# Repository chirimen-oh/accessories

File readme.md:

# Accessories for CHIRIMEN

They are hardware accessories of CHIRIMEN, all open source blueprints and can be used on the CHIRIMEN environment. They are mainly intended for use with CHIRIMEN for RPi, but  general purpose and can be used in other environments.

- [prot-hat](forRaspberryPi3/prot-hat/)
- [rpi3GpioTester](forRaspberryPi3/rpi3GpioTester/)
- [Grove-adt7410](grove/adt7410/)
- [Grove-s11059](grove/s11059/)
- [RPi2SeinsmartRelayIF](others/RPi2SeinsmartRelayIF/)
- [dcfan-guide](others/dcfan-guide/)
- [neopixel_i2c_TH](others/neopixel_i2c_TH/)

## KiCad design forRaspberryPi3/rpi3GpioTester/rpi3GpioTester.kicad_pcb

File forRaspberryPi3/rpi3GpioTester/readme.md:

# CHIRIMEN for RPi Full Test Board

### OSHW 
- [OSHWA UID: JP000006](https://certification.oshwa.org/jp000008.html)

CHIRIMEN for Raspberry Piの、[テストスイート](https://github.com/chirimen-oh/chirimen-raspi3/tree/master/gc/testSet)を一気に通すための試験用基板です。

それ以外にもRaspberry Piのブレークアウトボード的に便利に使えるかもしれません。

## Size

100x100mm  2layers

## Version

0.5 (KiCad version:5.1.4)

## 基板の発注

Elecrow等の基板製造サービスに、基板のサイズ(100x100mm)、Layer数(=2)、厚みや色(お好みで)など必要事項を記載の上、Gerberディレクトリの内容をアーカイブしたものを添付して発注します。[詳細は、Webで検索](https://www.google.com/search?q=elecrow+%E7%99%BA%E6%B3%A8%E6%96%B9%E6%B3%95)

## Parts

この基板に以下のパーツを半田付けしてご利用ください

- Raspberry Pi 接続用
  - 2x20 ピンソケット x1 - [秋月電子](http://akizukidenshi.com/catalog/g/gC-00085/)
    - あるいは 2x20 連結ピンソケット x1 - [秋月電子](http://akizukidenshi.com/catalog/g/gC-02485/), [スイッチサイエンス](https://www.switch-science.com/catalog/2022/)
    - あるいは 2x20 スタッキングコネクタ x 1 - [秋月電子](http://akizukidenshi.com/catalog/g/gC-10702/)
- GPIO 試験用
  - LED x 17 (3mm砲弾型で設計, 14+3 で 2 色にすると使いやすい)
  - LED 用抵抗 470Ω x 17 (LEDに流したい電流によって調整してください(1KΩぐらいまでは光ると思います))
  - タクトスイッチ (4本足、黒) x 14 - [秋月電子](http://akizukidenshi.com/catalog/g/gP-03647/), [Amazon](https://www.amazon.co.jp/dp/B07SYHP9B4/), [AliExpress](https://ja.aliexpress.com/item/32845984040.html)
  - タクトスイッチ (4本足、白) x 3 - [秋月電子](http://akizukidenshi.com/catalog/g/gP-03648/), [Amazon](https://www.amazon.co.jp/dp/B07SYZCL8Q/), [AliExpress](https://ja.aliexpress.com/item/32847703781.html)
- Grove 接続用
  - メスソケット x 4 - [千石通商](https://www.sengoku.co.jp/mod/sgk_cart/detail.php?code=EEHD-4KKK), [Switch Science](https://www.switch-science.com/catalog/1122/)
- I2C 接続用
  - 1x4 ピンソケット x 16 (I2C 用) - [秋月電子](http://akizukidenshi.com/catalog/g/gC-10099/)
    - note: 分割ロングピンソケットを分割してもよいが見栄えは悪くなる - [秋月電子](http://akizukidenshi.com/catalog/goods/search.aspx?search=x&keyword=fhu-1)
- その他の接続用
  - 1x20 ピンヘッダ x 1 - [秋月電子 (1x40 を分割)](http://akizukidenshi.com/catalog/g/gC-00167/)
    - あるいは 1x20 ピンソケット x1 - [秋月電子](http://akizukidenshi.com/catalog/g/gC-03077/)
  - 1x12 ピンヘッダ x 1 - [秋月電子 (1x40 を分割)](http://akizukidenshi.com/catalog/g/gC-00167/) 
    - あるいは 1x12 ピンソケット x1 - [秋月電子](http://akizukidenshi.com/catalog/g/gC-10101/)
  - 1x4 ピンヘッダ x 6 - [秋月電子 (1x40 を分割)](http://akizukidenshi.com/catalog/g/gC-00167/) 

I2C デバイス接続用に用意しておくと便利なもの
- 4pin ジャンパワイヤ - [秋月電子](https://ja.aliexpress.com/item/32812824461.html)

そのほか、試験対象とする I2C デバイス一式をご用意ください

## PCB Assembly

### 極性に注意するパーツ

- LED : 基板のパターンで、□(四角いランド)がGND(-)です (LEDの短い足を挿す)
- Grove : 写真を参考に
- 2x20ピンソケット : 裏側に取り付けます

### その他のはんだ付けの留意点

コネクタやピンヘッダは、まずピン一本だけはんだ付けした後、浮き上がりや、傾きなどをコテを当てながら修正した後に、残りの全ピンをはんだ付けするときれいに仕上がります。LEDやタクトスイッチ、抵抗器も同様に処理すると良いでしょう。

Grove や I2C 接続用ソケットはまとめてマスキングテープや養生テープで固定してから半田付けを行うとまとめて半田付けし易いです。

I2C, GND, 5V, 3.3V などをピンヘッダとピンソケットのいずれにするかは好み次第ですが、予定と違うものを付けないよう注意しましょう。

GPIO のプルアップ (PU) とプルダウン (PD) はお好み (と手元のパーツの都合) で LED やタクトスイッチの色を変えると見やすくなります。

### 組み立て例

## 回路図

## License

CC by 4.0

## OSHWA (オープンソースハードウェア) 認証ID
https://certification.oshwa.org/jp000006.html

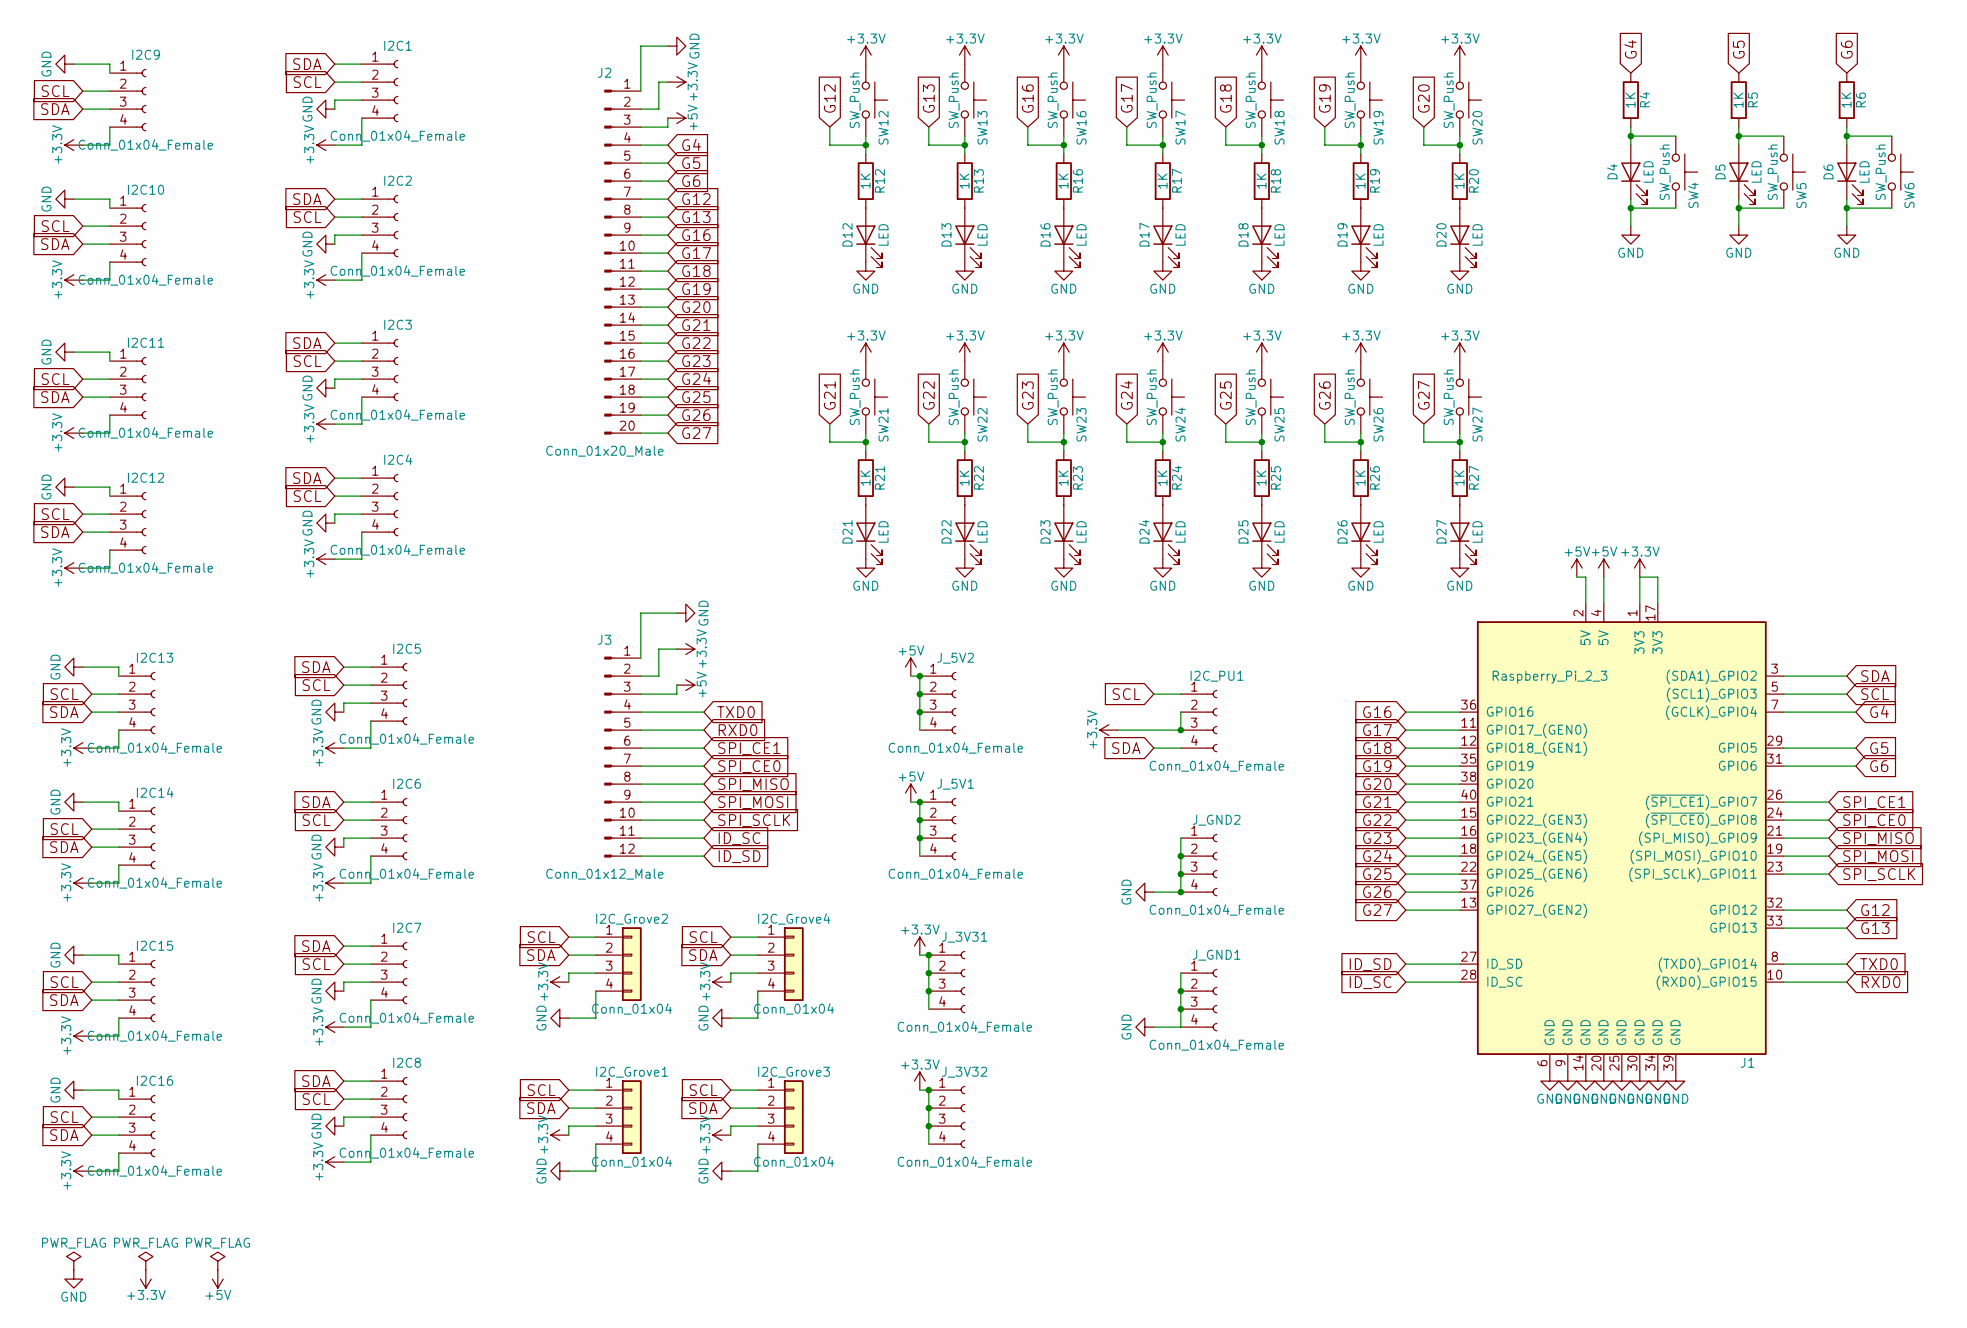
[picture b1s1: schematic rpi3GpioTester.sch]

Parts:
D4, D5, D6, D12, D13, D16, D17, D18, D19, D20, D21, D22, D23, D24, D25, D26, D27: LED; LED_D3.0mm
I2C1, I2C2, I2C3, I2C4, I2C5, I2C6, I2C7, I2C8, I2C9, I2C10, I2C11, I2C12, I2C13, I2C14, I2C15, I2C16, I2C_PU1: Conn_01x04_Female; Socket_Strip_Straight_1x04_Pitch2.54mm
I2C_Grove1, I2C_Grove2, I2C_Grove3, I2C_Grove4: Conn_01x04; Grove_1x04
J1: Raspberry_Pi_2_3; Socket_Strip_Straight_2x20_Pitch2.54mm
J2: Conn_01x20_Male; Pin_Header_Straight_1x20_Pitch2.54mm
J3: Conn_01x12_Male; Pin_Header_Straight_1x12_Pitch2.54mm
J_3V31, J_3V32, J_5V1, J_5V2: Conn_01x04_Female; Socket_Strip_Straight_1x04_Pitch2.54mm
J_GND1, J_GND2: Conn_01x04_Female; Socket_Strip_Straight_1x04_Pitch2.54mm
R4, R5, R6, R12, R13, R16, R17, R18, R19, R20, R21, R22, R23, R24, R25, R26, R27: 1K; R_Axial_DIN0207_L6.3mm_D2.5mm_P2.54mm_Vertical
SW4, SW5, SW6, SW12, SW13, SW16, SW17, SW18, SW19, SW20, SW21, SW22, SW23, SW24, SW25, SW26, SW27: SW_Push; SW_Tactile_Straight_KSA0Axx1LFTR

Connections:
+3V3: I2C1.4, I2C2.4, I2C3.4, I2C4.4, I2C5.4, I2C6.4, I2C7.4, I2C8.4, I2C9.4, I2C10.4, I2C11.4, I2C12.4, I2C13.4, I2C14.4, I2C15.4, I2C16.4, I2C_Grove1.3, I2C_Grove2.3, I2C_Grove3.3, I2C_Grove4.3, I2C_PU1.2, I2C_PU1.3, J1.1 (3V3), J1.17 (3V3), J2.2, J3.2, J_3V31.1, J_3V31.2, J_3V31.3, J_3V31.4, J_3V32.1, J_3V32.2, J_3V32.3, J_3V32.4, SW12.1, SW13.1, SW16.1, SW17.1, SW18.1, SW19.1, SW20.1, SW21.1, SW22.1, SW23.1, SW24.1, SW25.1, SW26.1, SW27.1
+5V: J1.2 (5V), J1.4 (5V), J2.3, J3.3, J_5V1.1, J_5V1.2, J_5V1.3, J_5V1.4, J_5V2.1, J_5V2.2, J_5V2.3, J_5V2.4
G4: J1.7 ((GCLK)_GPIO4), J2.4, R4.1
G5: J1.29 (GPIO5), J2.5, R5.1
G6: J1.31 (GPIO6), J2.6, R6.1
G12: J1.32 (GPIO12), J2.7, R12.1, SW12.2
G13: J1.33 (GPIO13), J2.8, R13.1, SW13.2
G16: J1.36 (GPIO16), J2.9, R16.1, SW16.2
G17: J1.11 (GPIO17_(GEN0)), J2.10, R17.1, SW17.2
G18: J1.12 (GPIO18_(GEN1)), J2.11, R18.1, SW18.2
G19: J1.35 (GPIO19), J2.12, R19.1, SW19.2
G20: J1.38 (GPIO20), J2.13, R20.1, SW20.2
G21: J1.40 (GPIO21), J2.14, R21.1, SW21.2
G22: J1.15 (GPIO22_(GEN3)), J2.15, R22.1, SW22.2
G23: J1.16 (GPIO23_(GEN4)), J2.16, R23.1, SW23.2
G24: J1.18 (GPIO24_(GEN5)), J2.17, R24.1, SW24.2
G25: J1.22 (GPIO25_(GEN6)), J2.18, R25.1, SW25.2
G26: J1.37 (GPIO26), J2.19, R26.1, SW26.2
G27: J1.13 (GPIO27_(GEN2)), J2.20, R27.1, SW27.2
GND: D4.1 (K), D5.1 (K), D6.1 (K), D12.1 (K), D13.1 (K), D16.1 (K), D17.1 (K), D18.1 (K), D19.1 (K), D20.1 (K), D21.1 (K), D22.1 (K), D23.1 (K), D24.1 (K), D25.1 (K), D26.1 (K), D27.1 (K), I2C1.3, I2C2.3, I2C3.3, I2C4.3, I2C5.3, I2C6.3, I2C7.3, I2C8.3, I2C9.1, I2C10.1, I2C11.1, I2C12.1, I2C13.1, I2C14.1, I2C15.1, I2C16.1, I2C_Grove1.4, I2C_Grove2.4, I2C_Grove3.4, I2C_Grove4.4, J1.6 (GND), J1.9 (GND), J1.14 (GND), J1.20 (GND), J1.25 (GND), J1.30 (GND), J1.34 (GND), J1.39 (GND), J2.1, J3.1, J_GND1.1, J_GND1.2, J_GND1.3, J_GND1.4, J_GND2.1, J_GND2.2, J_GND2.3, J_GND2.4, SW4.2, SW5.2, SW6.2
ID_SC: J1.28 (ID_SC), J3.11
ID_SD: J1.27 (ID_SD), J3.12
unnamed: D4.2 (A), R4.2, SW4.1
unnamed: D5.2 (A), R5.2, SW5.1
unnamed: D6.2 (A), R6.2, SW6.1
unnamed: D12.2 (A), R12.2
unnamed: D13.2 (A), R13.2
unnamed: D16.2 (A), R16.2
unnamed: D17.2 (A), R17.2
unnamed: D18.2 (A), R18.2
unnamed: D19.2 (A), R19.2
unnamed: D20.2 (A), R20.2
unnamed: D21.2 (A), R21.2
unnamed: D22.2 (A), R22.2
unnamed: D23.2 (A), R23.2
unnamed: D24.2 (A), R24.2
unnamed: D25.2 (A), R25.2
unnamed: D26.2 (A), R26.2
unnamed: D27.2 (A), R27.2
RXD0: J1.10 ((RXD0)_GPIO15), J3.5
SCL: I2C1.2, I2C2.2, I2C3.2, I2C4.2, I2C5.2, I2C6.2, I2C7.2, I2C8.2, I2C9.2, I2C10.2, I2C11.2, I2C12.2, I2C13.2, I2C14.2, I2C15.2, I2C16.2, I2C_Grove1.1, I2C_Grove2.1, I2C_Grove3.1, I2C_Grove4.1, I2C_PU1.1, J1.5 ((SCL1)_GPIO3)
SDA: I2C1.1, I2C2.1, I2C3.1, I2C4.1, I2C5.1, I2C6.1, I2C7.1, I2C8.1, I2C9.3, I2C10.3, I2C11.3, I2C12.3, I2C13.3, I2C14.3, I2C15.3, I2C16.3, I2C_Grove1.2, I2C_Grove2.2, I2C_Grove3.2, I2C_Grove4.2, I2C_PU1.4, J1.3 ((SDA1)_GPIO2)
SPI_CE0: J1.24 ((~SPI_CE0~)_GPIO8), J3.7
SPI_CE1: J1.26 ((~SPI_CE1~)_GPIO7), J3.6
SPI_MISO: J1.21 ((SPI_MISO)_GPIO9), J3.8
SPI_MOSI: J1.19 ((SPI_MOSI)_GPIO10), J3.9
SPI_SCLK: J1.23 ((SPI_SCLK)_GPIO11), J3.10
TXD0: J1.8 ((TXD0)_GPIO14), J3.4

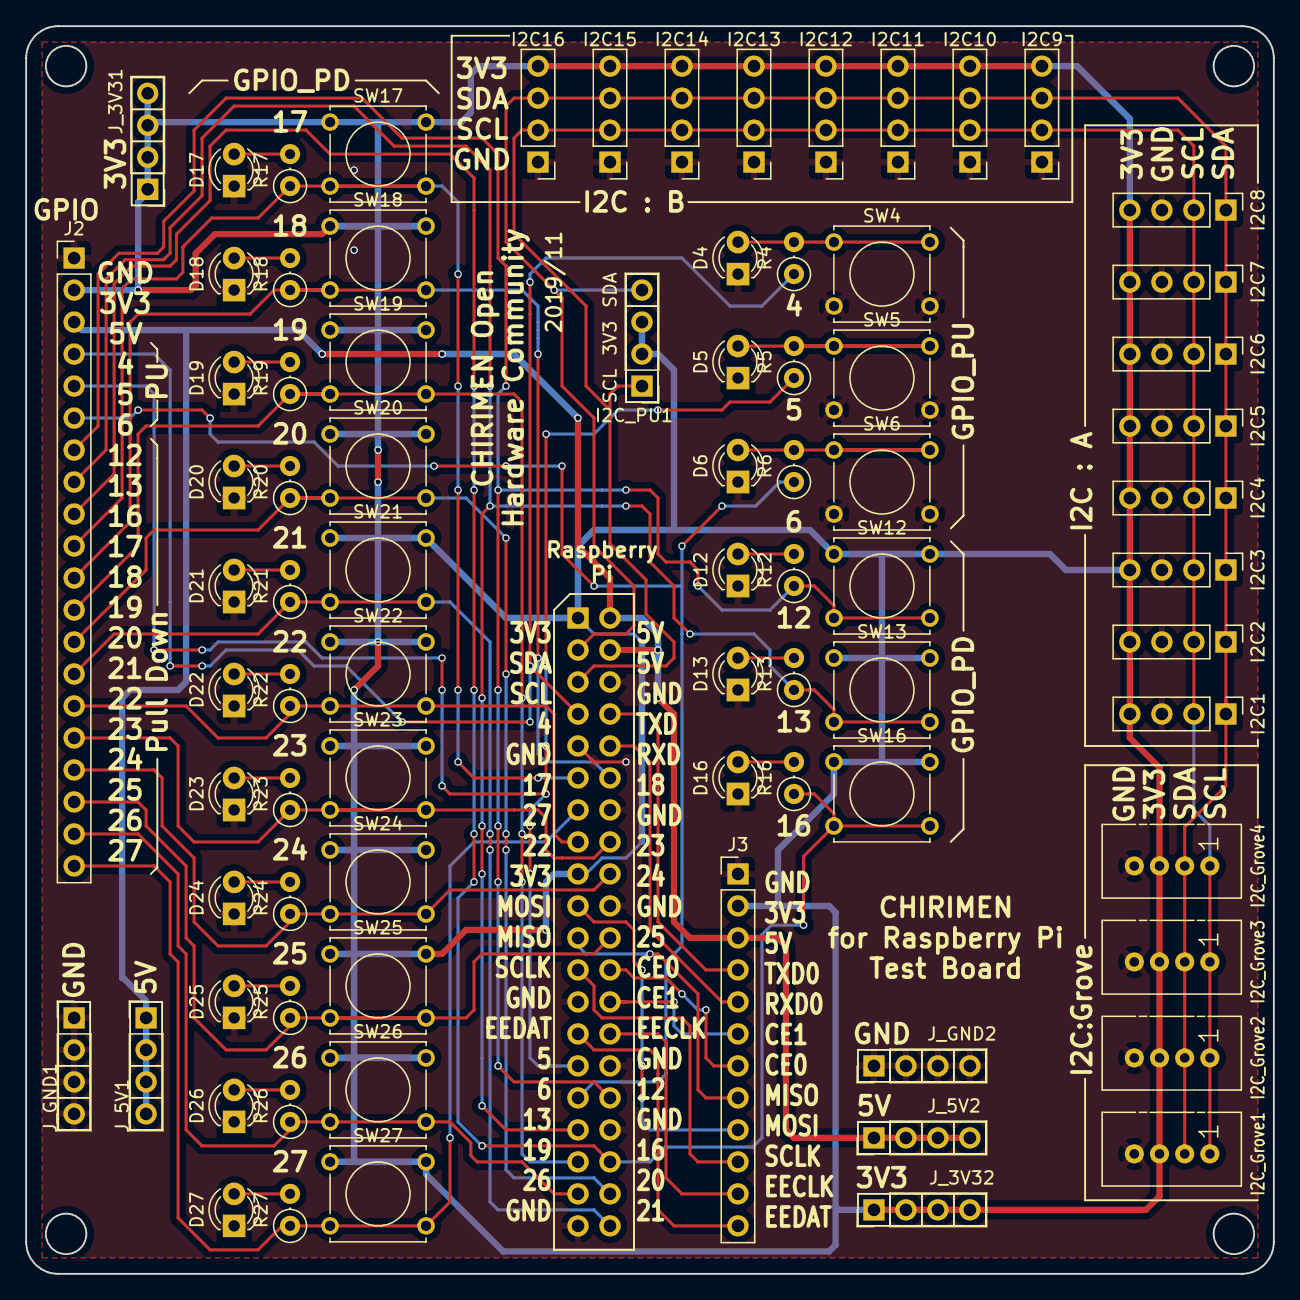
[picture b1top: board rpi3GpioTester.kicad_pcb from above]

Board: 2 copper layers, 99.1 x 99.1 mm, 81 parts (1 on the bottom side), 48 nets.

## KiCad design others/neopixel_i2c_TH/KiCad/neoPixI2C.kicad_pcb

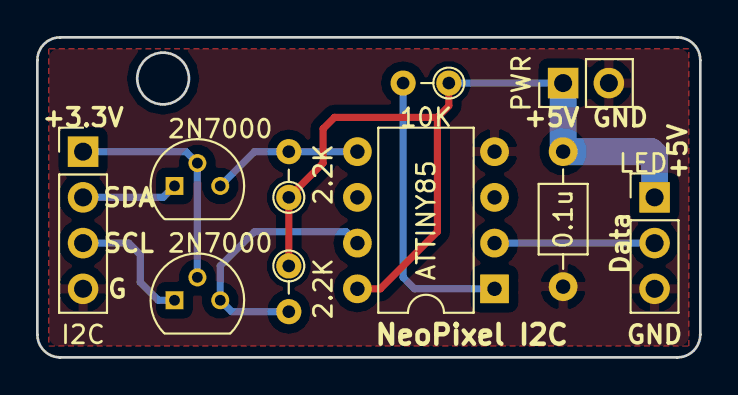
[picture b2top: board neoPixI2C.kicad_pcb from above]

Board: 2 copper layers, 36.8 x 17.8 mm, 10 parts (0 on the bottom side), 9 nets.

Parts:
0.1u: 0.1μ; C_Axial_L3.8mm_D2.6mm_P7.50mm_Horizontal
2.2K, 2.2K#2: 2.2K; R_Axial_DIN0204_L3.6mm_D1.6mm_P2.54mm_Vertical
2N7000, 2N7000#2: 2N7000; TO-92_Molded_Narrow
10K: 10K; R_Axial_DIN0204_L3.6mm_D1.6mm_P2.54mm_Vertical
ATTINY85: ATTINY85-20PU; DIP-8_W7.62mm
I2C: I2C; Pin_Header_Straight_1x04_Pitch2.54mm
LED: LED; Pin_Header_Straight_1x03_Pitch2.54mm
PWR: POWER; Pin_Header_Straight_1x02_Pitch2.54mm

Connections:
+5V: 0.1u.1, 2.2K.1, 2.2K#2.1, 10K.1, ATTINY85.8, LED.1, PWR.1
GND: 0.1u.2, ATTINY85.4, I2C.4, LED.3, PWR.2
unnamed: ATTINY85.2, LED.2
unnamed: 2N7000.2, 2N7000#2.2, I2C.1
unnamed: 2N7000.1, I2C.2
unnamed: 2N7000#2.1, I2C.3
unnamed: 2.2K#2.2, 2N7000.3, ATTINY85.5
unnamed: 2.2K.2, 2N7000#2.3, ATTINY85.7
unnamed: 10K.2, ATTINY85.1

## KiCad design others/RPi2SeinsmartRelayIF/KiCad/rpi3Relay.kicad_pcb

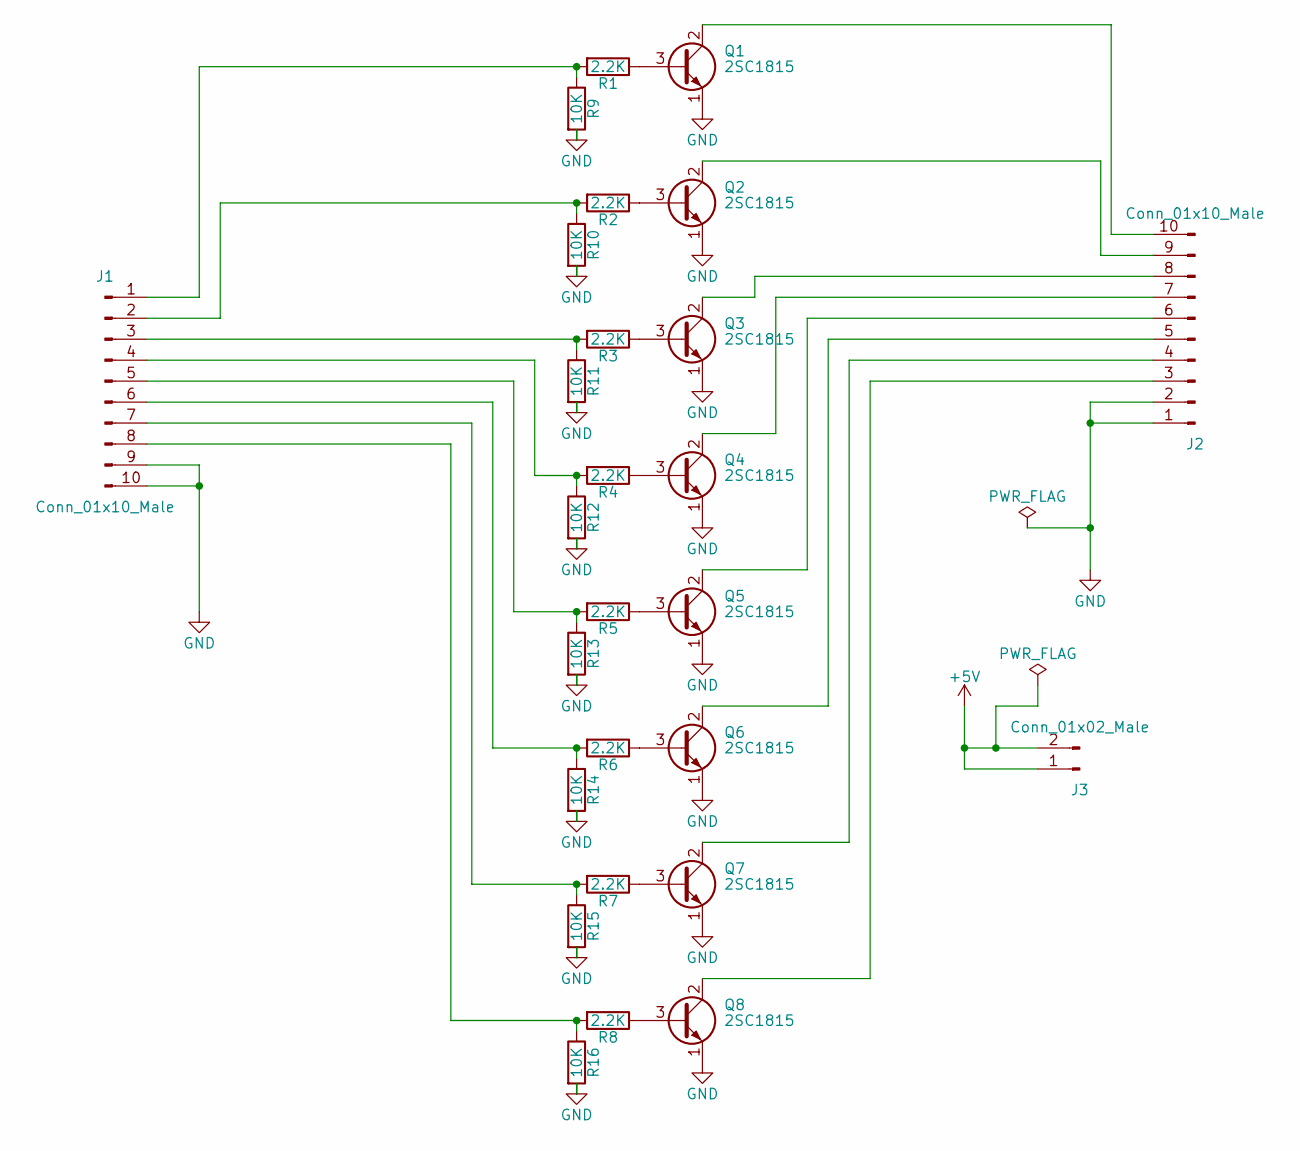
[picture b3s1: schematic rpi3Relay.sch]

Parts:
J1, J2: Conn_01x10_Male; Pin_Header_Straight_1x10_Pitch2.54mm
J3: Conn_01x02_Male; Pin_Header_Straight_1x02_Pitch2.54mm
Q1, Q2, Q3, Q4, Q5, Q6, Q7, Q8: 2SC1815; TO-92_Molded_Narrow
R1, R2, R3, R4, R5, R6, R7, R8: 2.2K; R_Axial_DIN0204_L3.6mm_D1.6mm_P1.90mm_Vertical
R9, R10, R11, R12, R13, R14, R15, R16: 10K; R_Axial_DIN0204_L3.6mm_D1.6mm_P1.90mm_Vertical

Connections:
+5V: J3.1, J3.2
GND: J1.9, J1.10, J2.1, J2.2, Q1.1 (E), Q2.1 (E), Q3.1 (E), Q4.1 (E), Q5.1 (E), Q6.1 (E), Q7.1 (E), Q8.1 (E), R9.2, R10.2, R11.2, R12.2, R13.2, R14.2, R15.2, R16.2
unnamed: J1.1, R1.2, R9.1
unnamed: J1.2, R2.2, R10.1
unnamed: J1.3, R3.2, R11.1
unnamed: J1.4, R4.2, R12.1
unnamed: J1.5, R5.2, R13.1
unnamed: J1.6, R6.2, R14.1
unnamed: J1.7, R7.2, R15.1
unnamed: J1.8, R8.2, R16.1
unnamed: J2.3, Q8.2 (C)
unnamed: J2.4, Q7.2 (C)
unnamed: J2.5, Q6.2 (C)
unnamed: J2.6, Q5.2 (C)
unnamed: J2.7, Q4.2 (C)
unnamed: J2.8, Q3.2 (C)
unnamed: J2.9, Q2.2 (C)
unnamed: J2.10, Q1.2 (C)
unnamed: Q1.3 (B), R1.1
unnamed: Q2.3 (B), R2.1
unnamed: Q3.3 (B), R3.1
unnamed: Q4.3 (B), R4.1
unnamed: Q5.3 (B), R5.1
unnamed: Q6.3 (B), R6.1
unnamed: Q7.3 (B), R7.1
unnamed: Q8.3 (B), R8.1

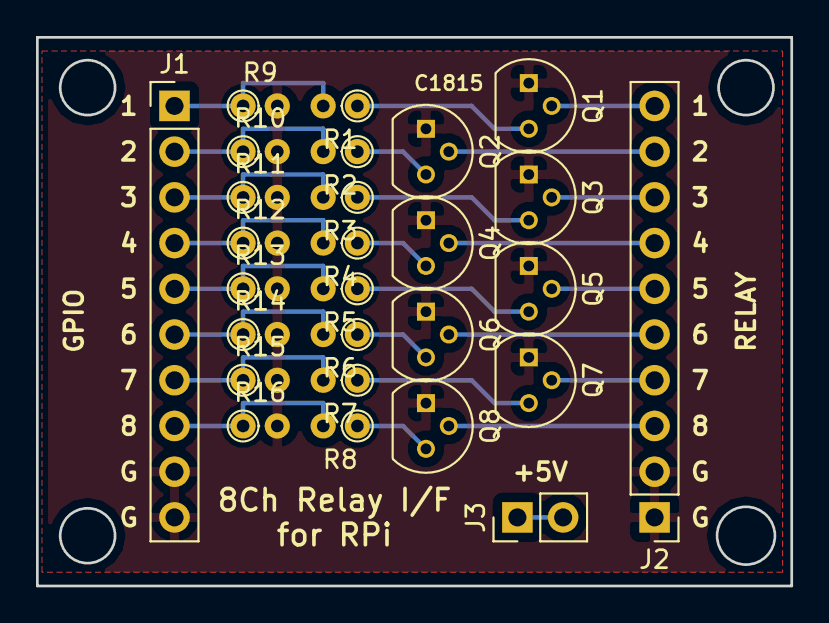
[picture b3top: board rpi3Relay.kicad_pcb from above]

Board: 2 copper layers, 41.9 x 30.5 mm, 27 parts (0 on the bottom side), 26 nets.

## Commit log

2017-12-04 add image
2018-02-28 add grove/adt7410 and grove/s11059
2018-07-10 add dcfan guide
2019-11-18 Update tester board
2019-11-20 Update rpi3GpioTester pcb design
2019-11-20 Board.png
2019-11-21 rpi3GpioTester rev0.3
2019-11-22 Add I2C pull up pattern
2019-11-22 Minor update
2019-11-25 Update rpi3GpioTester
2019-11-28 rpi3GpioTester 10x10cm design change...
2019-11-28 rpi3GpioTester minor change
2019-12-02 add parts list
2019-12-06 rpiGpioTester silk update
2019-12-15 chirimen test board photo
2019-12-15 rotate photo
2019-12-17 Add schematic img
2020-01-25 Create LICENSE
2020-01-25 Update LICENSE
2021-02-06 OSHWA UID add
2022-09-11 LED の色分けについて追記
2024-08-20 change link url
